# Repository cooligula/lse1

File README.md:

View this project on [CADLAB.io](https://cadlab.io/project/29478). 

# LSE1
> [!CAUTION]
> **NO FABRICAR** 

Aquesta PCB no respecta les regles de disseny de SafePCB donat que es va fer per a ser fabricada amb JLCPCB durant l'estiu.

A més, per tal com estan definits els rangs de preu a JLCPCB, es va prendre la decisió conscient de fer la placa més gran que el que es demana a l'assignatura, ja que no suposava un sobrecost si no superava els 100mm x 100mm.

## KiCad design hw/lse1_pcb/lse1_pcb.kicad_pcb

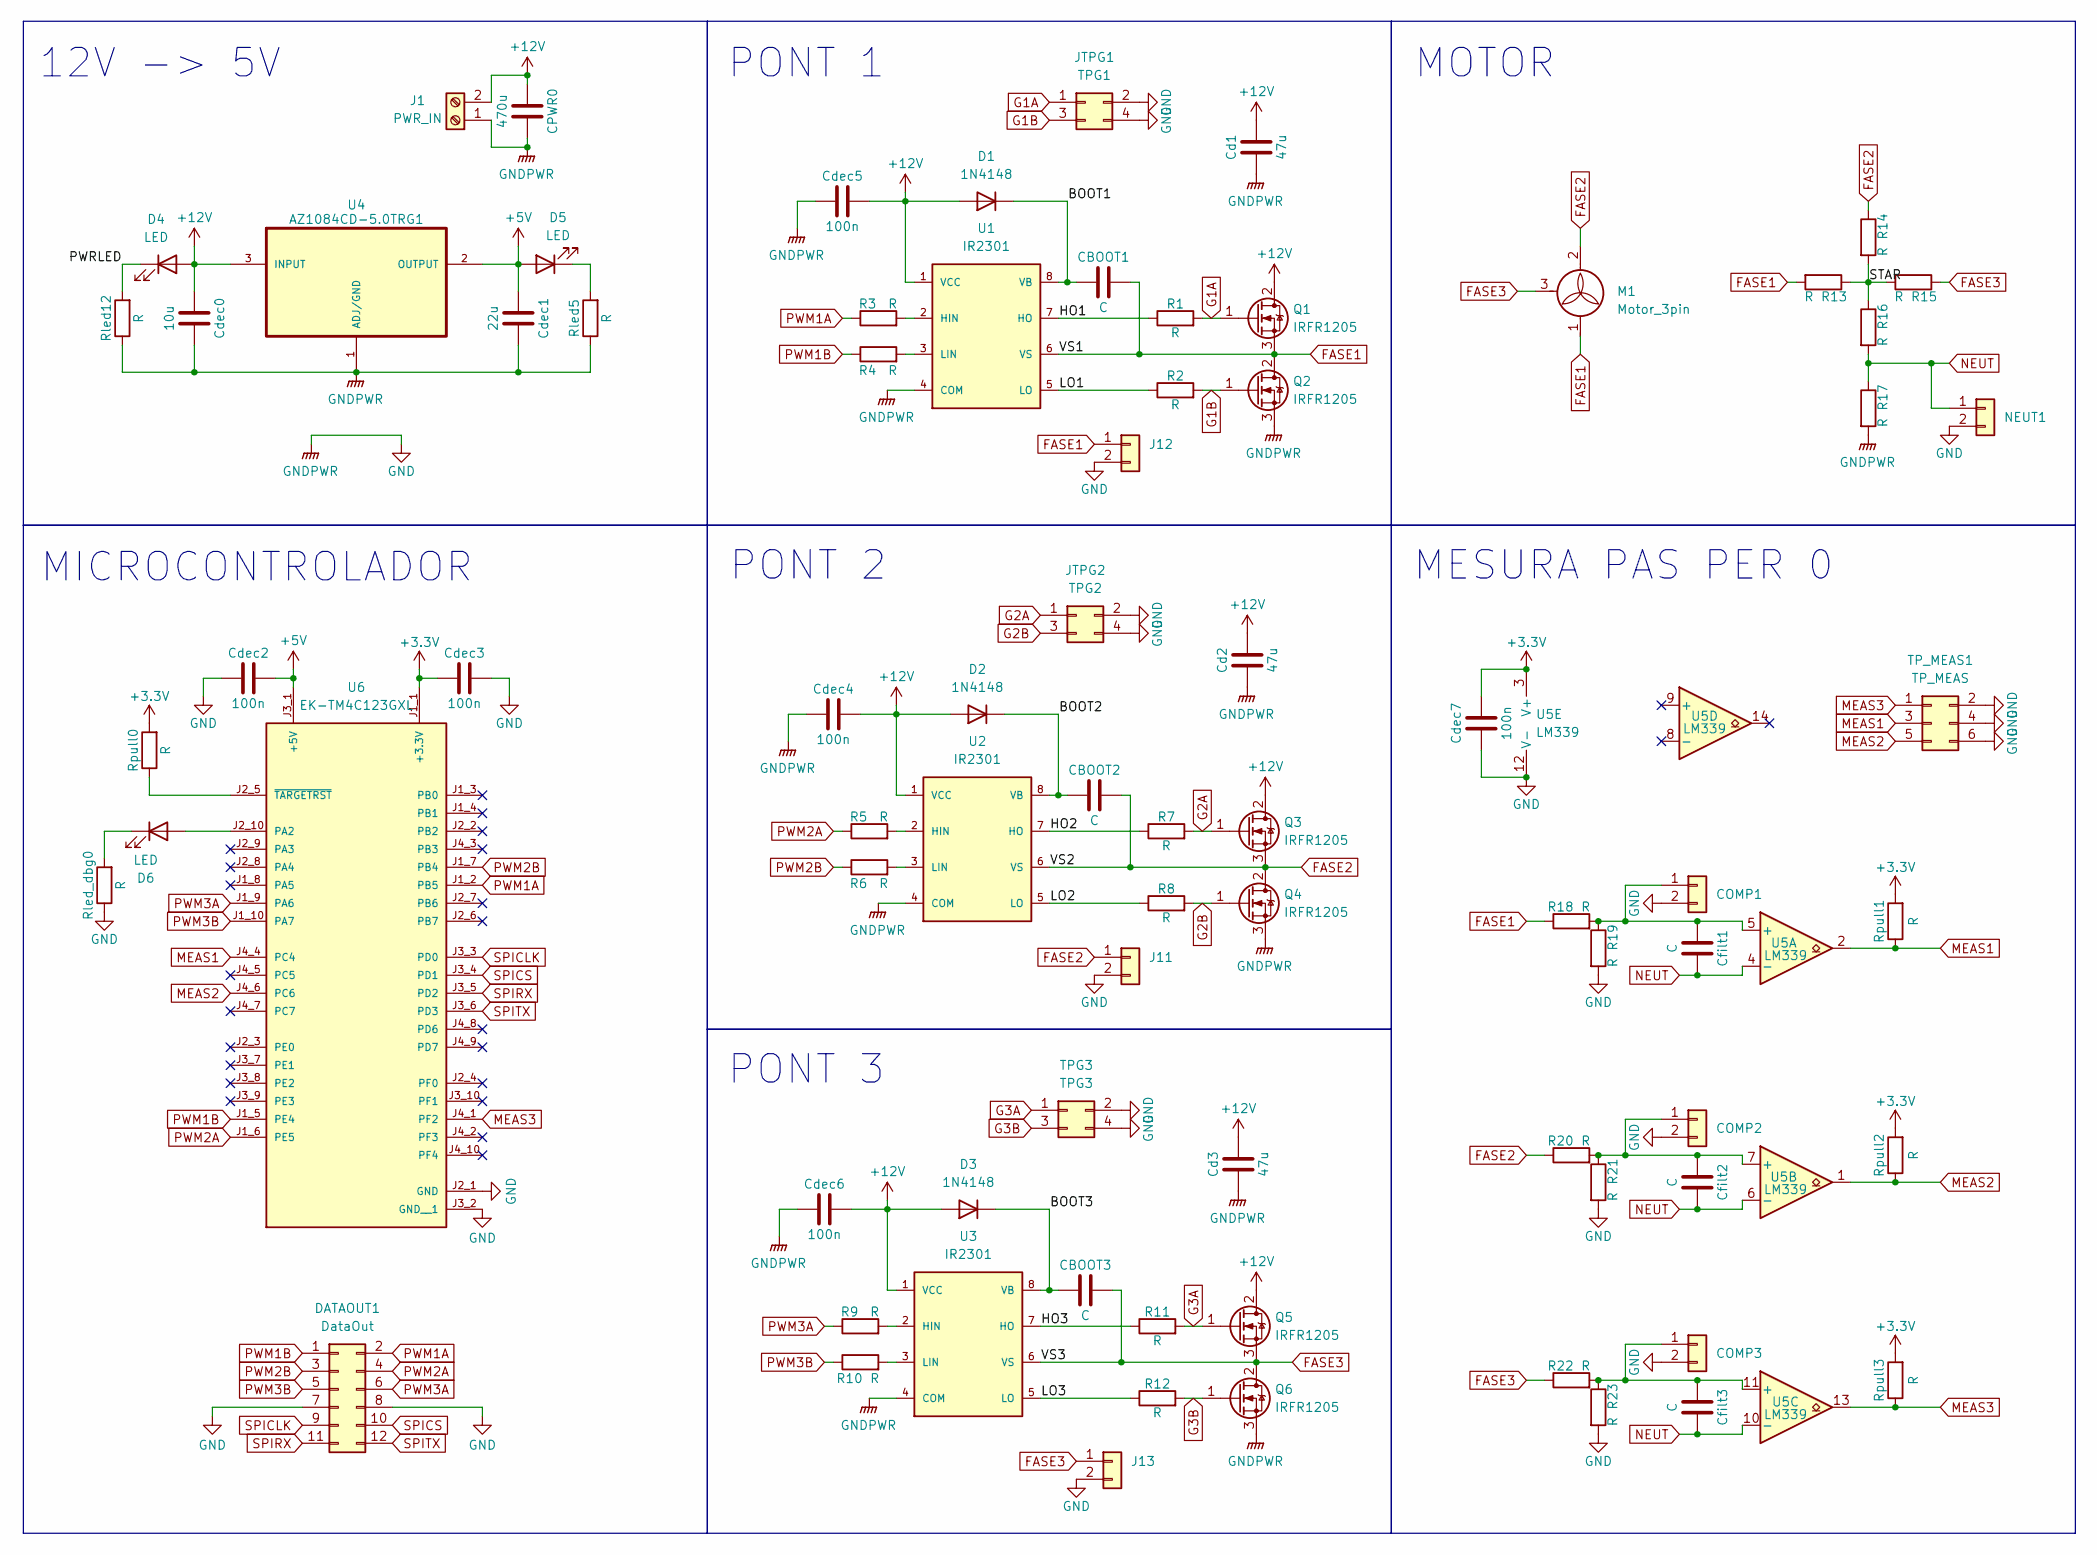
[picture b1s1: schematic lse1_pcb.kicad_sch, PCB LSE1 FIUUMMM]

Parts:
CBOOT1, CBOOT2, CBOOT3: C; C_1206_3216Metric
COMP1: TP_DIV1; PinHeader_1x02_P2.54mm_Vertical
COMP2: TP_DIV2; PinHeader_1x02_P2.54mm_Vertical
COMP3: TP_DIV3; PinHeader_1x02_P2.54mm_Vertical
CPWR0: 470u; C_Elec_10x10.2
Cd1, Cd2, Cd3: 47u; C_1206_3216Metric
Cdec0: 10u; C_1206_3216Metric
Cdec1: 22u; C_1206_3216Metric
Cdec2, Cdec3, Cdec4, Cdec5, Cdec6, Cdec7: 100n; C_1206_3216Metric
Cfilt1, Cfilt2, Cfilt3: C; C_1206_3216Metric
D1, D2, D3: 1N4148; D_DO-35_SOD27_P7.62mm_Horizontal
D4, D5, D6: LED; LED_0805_2012Metric
DATAOUT1: DataOut; PinHeader_2x06_P2.54mm_Vertical
J1: PWR_IN; Samtec_HPM-02-01-x-S_Straight_1x02_Pitch5.08mm
J11: TP_FASE2; PinHeader_1x02_P2.54mm_Vertical
J12: TP_FASE1; PinHeader_1x02_P2.54mm_Vertical
J13: TP_FASE3; PinHeader_1x02_P2.54mm_Vertical
JTPG1: TPG1; PinHeader_1x04_P2.54mm_Vertical
JTPG2: TPG2; PinHeader_1x04_P2.54mm_Vertical
M1: Motor_3pin; Samtec_HPM-03-01-x-S_Straight_1x03_Pitch5.08mm
NEUT1: TP_NEUT; PinHeader_1x02_P2.54mm_Vertical
Q1, Q2, Q3, Q4, Q5, Q6: IRFR1205; TO-252-2
R1, R2, R3, R4, R5, R6, R7, R8, R9, R10, R11, R12, R13, R14, R15, R16, R17, R18, R19, R20, R21, R22, R23: R; R_1206_3216Metric
Rled5, Rled12: R; R_1206_3216Metric
Rled_dbg0: R; R_1206_3216Metric
Rpull0, Rpull1, Rpull2, Rpull3: R; R_1206_3216Metric
TPG3: TPG3; PinHeader_1x04_P2.54mm_Vertical
TP_MEAS1: TP_MEAS; PinHeader_2x03_P2.54mm_Vertical
U1, U2, U3: IR2301; SOIC-8_3.9x4.9mm_P1.27mm
U4: AZ1084CD-5.0TRG1; DPAK457P1010X238-3N
U5: LM339; SOIC-14_3.9x8.7mm_P1.27mm
U6: EK-TM4C123GXL; MODULE_EK-TM4C123GXL; PARTREV April 2013

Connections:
+3.3V: Cdec3.1, Cdec7.2, Rpull0.2, Rpull1.2, Rpull2.2, Rpull3.2, U5.3 (V+), U6.J1_1 (+3.3V)
+5V: Cdec1.1, Cdec2.2, D5.2 (A), U4.2 (OUTPUT), U6.J3_1 (+5V)
+12V: CPWR0.1, Cd1.2, Cd2.2, Cd3.2, Cdec0.1, Cdec4.2, Cdec5.2, Cdec6.2, D1.2 (A), D2.2 (A), D3.2 (A), D4.2 (A), J1.2, Q1.2 (D), Q3.2 (D), Q5.2 (D), U1.1 (VCC), U2.1 (VCC), U3.1 (VCC), U4.3 (INPUT)
/BOOT1: CBOOT1.1, D1.1 (K), U1.8 (VB)
/BOOT2: CBOOT2.1, D2.1 (K), U2.8 (VB)
/BOOT3: CBOOT3.1, D3.1 (K), U3.8 (VB)
/HO1: R1.1, U1.7 (HO)
/HO2: R7.1, U2.7 (HO)
/HO3: R11.1, U3.7 (HO)
/LO1: R2.1, U1.5 (LO)
/LO2: R8.1, U2.5 (LO)
/LO3: R12.1, U3.5 (LO)
/PWRLED: D4.1 (K), Rled12.2
/STAR: R13.1, R14.2, R15.2, R16.1
FASE1: CBOOT1.2, J12.1, M1.1, Q1.3 (S), Q2.2 (D), R13.2, R18.1, U1.6 (VS)
FASE2: CBOOT2.2, J11.1, M1.2, Q3.3 (S), Q4.2 (D), R14.1, R20.1, U2.6 (VS)
FASE3: CBOOT3.2, J13.1, M1.3, Q5.3 (S), Q6.2 (D), R15.1, R22.1, U3.6 (VS)
G1A: JTPG1.1, Q1.1 (G), R1.2
G1B: JTPG1.3, Q2.1 (G), R2.2
G2A: JTPG2.1, Q3.1 (G), R7.2
G2B: JTPG2.3, Q4.1 (G), R8.2
G3A: Q5.1 (G), R11.2, TPG3.1
G3B: Q6.1 (G), R12.2, TPG3.3
GND: COMP1.2, COMP2.2, COMP3.2, CPWR0.2, Cd1.1, Cd2.1, Cd3.1, Cdec0.2, Cdec1.2, Cdec2.1, Cdec3.2, Cdec4.1, Cdec5.1, Cdec6.1, Cdec7.1, DATAOUT1.7, DATAOUT1.8, J1.1, J11.2, J12.2, J13.2, JTPG1.2, JTPG1.4, JTPG2.2, JTPG2.4, NEUT1.2, Q2.3 (S), Q4.3 (S), Q6.3 (S), R17.2, R19.2, R21.2, R23.2, Rled5.1, Rled12.1, Rled_dbg0.1, TPG3.2, TPG3.4, TP_MEAS1.2, TP_MEAS1.4, TP_MEAS1.6, U1.4 (COM), U2.4 (COM), U3.4 (COM), U4.1 (ADJ/GND), U5.12 (V-), U6.J2_1 (GND), U6.J3_2 (GND__1); also elsewhere on the board
MEAS1: Rpull1.1, TP_MEAS1.3, U5.2, U6.J4_4 (PC4); also elsewhere on the board
MEAS2: Rpull2.1, TP_MEAS1.5, U5.1, U6.J4_6 (PC6); also elsewhere on the board
MEAS3: Rpull3.1, TP_MEAS1.1, U5.13, U6.J4_1 (PF2); also elsewhere on the board
NEUT: Cfilt1.2, Cfilt2.2, Cfilt3.2, NEUT1.1, R16.2, R17.1, U5.4 (-), U5.6 (-), U5.10 (-)
unnamed: COMP1.1, Cfilt1.1, R18.2, R19.1, U5.5 (+)
unnamed: COMP2.1, Cfilt2.1, R20.2, R21.1, U5.7 (+)
unnamed: COMP3.1, Cfilt3.1, R22.2, R23.1, U5.11 (+)
unnamed: D5.1 (K), Rled5.2
unnamed: D6.2 (A), U6.J2_10 (PA2)
unnamed: D6.1 (K), Rled_dbg0.2
unnamed: R3.2, U1.2 (HIN)
unnamed: R4.2, U1.3 (LIN)
unnamed: R5.2, U2.2 (HIN)
unnamed: R6.2, U2.3 (LIN)
unnamed: R9.2, U3.2 (HIN)
unnamed: R10.2, U3.3 (LIN)
unnamed: Rpull0.1, U6.J2_5 (~TARGETRST)
PWM1A: DATAOUT1.2, R3.1, U6.J1_2 (PB5)
PWM1B: DATAOUT1.1, R4.1, U6.J1_5 (PE4)
PWM2A: DATAOUT1.4, R5.1, U6.J1_6 (PE5)
PWM2B: DATAOUT1.3, R6.1, U6.J1_7 (PB4)
PWM3A: DATAOUT1.6, R9.1, U6.J1_9 (PA6)
PWM3B: DATAOUT1.5, R10.1, U6.J1_10 (PA7)
SPICLK: DATAOUT1.9, U6.J3_3 (PD0)
SPICS: DATAOUT1.10, U6.J3_4 (PD1)
SPIRX: DATAOUT1.11, U6.J3_5 (PD2)
SPITX: DATAOUT1.12, U6.J3_6 (PD3)

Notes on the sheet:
PONT 1
12V -> 5V
MOTOR
PONT 3
MESURA PAS PER 0
PONT 2
MICROCONTROLADOR

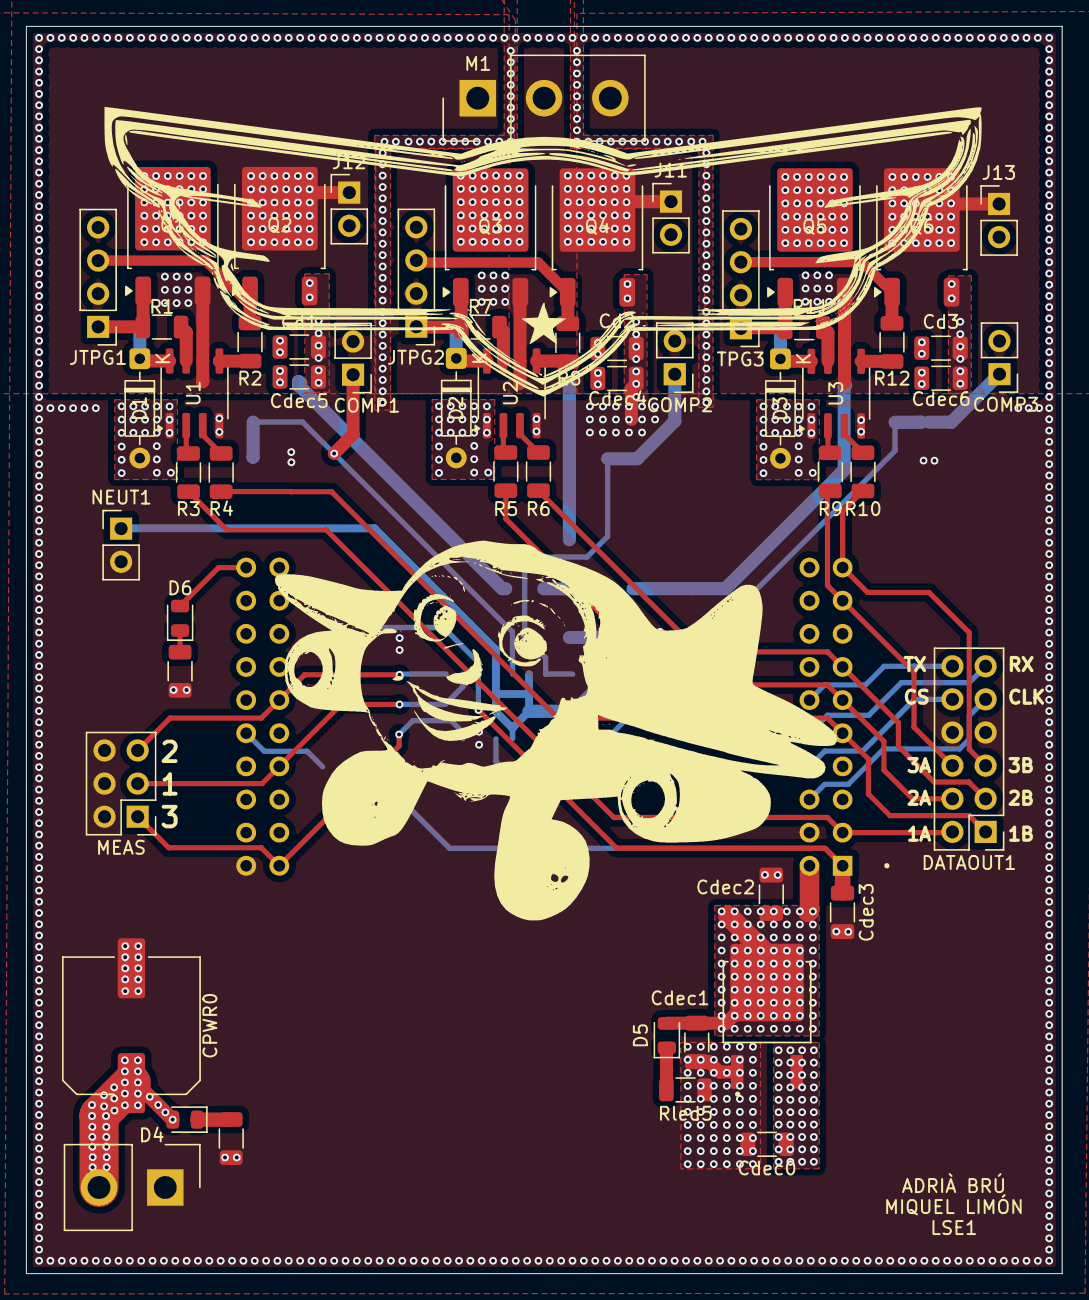
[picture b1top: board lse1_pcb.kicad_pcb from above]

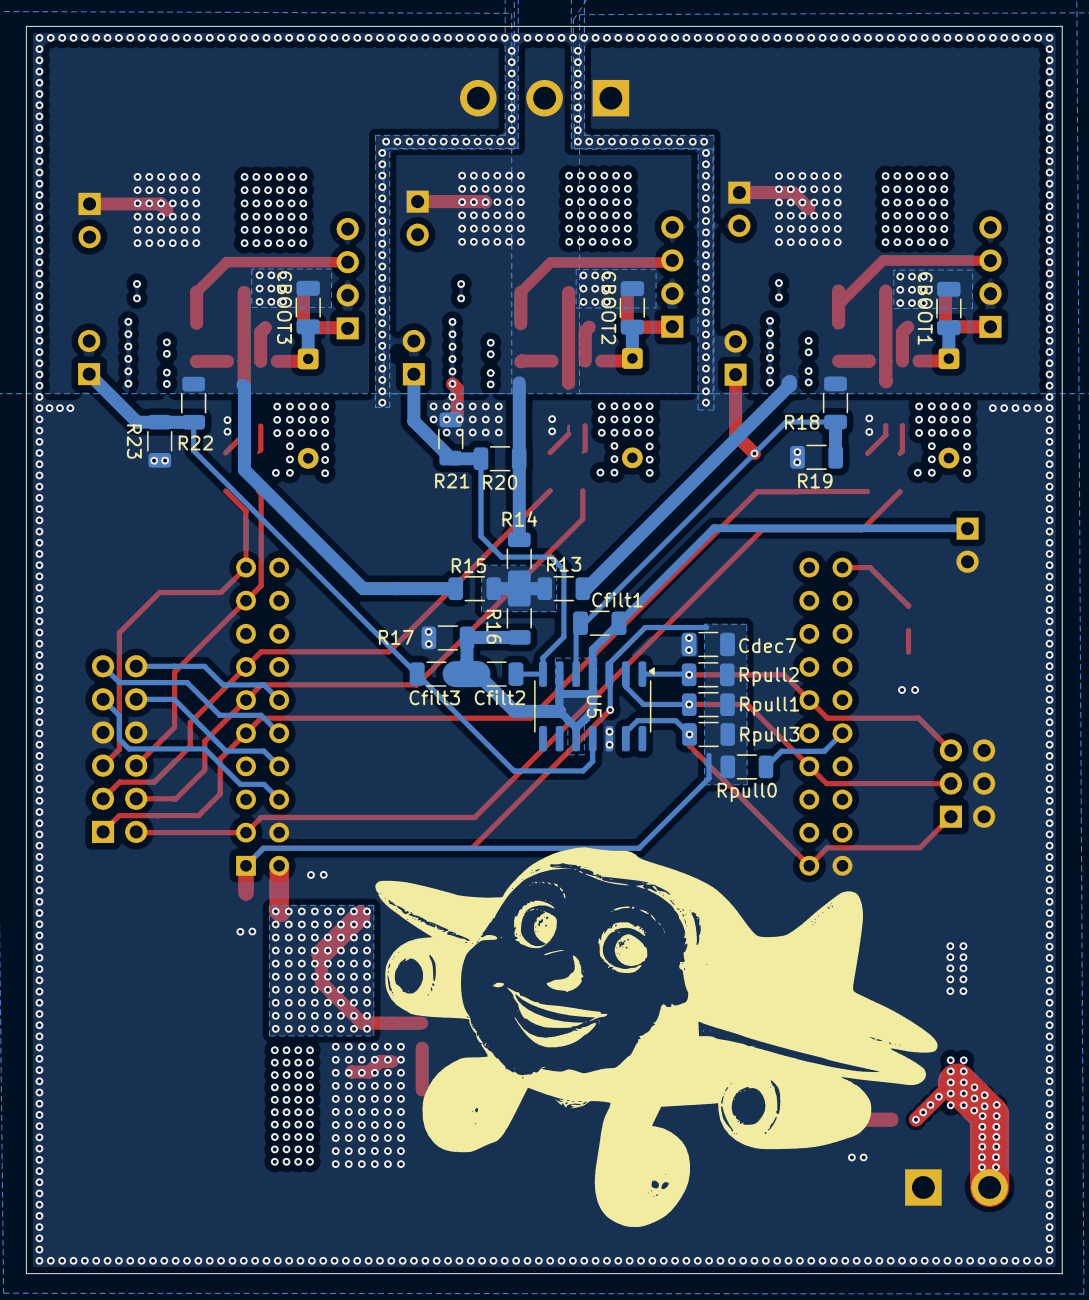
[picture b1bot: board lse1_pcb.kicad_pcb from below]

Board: 4 copper layers, 79.4 x 95.6 mm, 80 parts (23 on the bottom side), 51 nets.

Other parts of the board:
MEAS: TP_MEAS; PinHeader_2x03_P2.54mm_Vertical

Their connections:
GND: MEAS.2, MEAS.4, MEAS.6; also elsewhere on the board
MEAS1: MEAS.3; also elsewhere on the board
MEAS2: MEAS.5; also elsewhere on the board
MEAS3: MEAS.1; also elsewhere on the board

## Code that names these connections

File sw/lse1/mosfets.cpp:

#include "mosfets.h"
#include "driverlib/pin_map.h"

void MosfetController::setup(uint32_t pwm_freq, float duty_cycle)
{
    // The PWM peripheral must be enabled for use.
    // Habilitem els moduls 0 i 1 pq els necessitem els dos
    MAP_SysCtlPeripheralEnable(SYSCTL_PERIPH_PWM0);
    MAP_SysCtlPeripheralEnable(SYSCTL_PERIPH_PWM1);

    // Enable the GPIO port that is used for the PWM output.
    MAP_SysCtlPeripheralEnable(SYSCTL_PERIPH_GPIOA);
    MAP_SysCtlPeripheralEnable(SYSCTL_PERIPH_GPIOB);
    MAP_SysCtlPeripheralEnable(SYSCTL_PERIPH_GPIOE);

    // Wait for peripherals to be ready
    while(!MAP_SysCtlPeripheralReady(SYSCTL_PERIPH_GPIOA) ||
          !MAP_SysCtlPeripheralReady(SYSCTL_PERIPH_GPIOB) ||
          !MAP_SysCtlPeripheralReady(SYSCTL_PERIPH_GPIOE) ||
          !MAP_SysCtlPeripheralReady(SYSCTL_PERIPH_PWM0)  ||
          !MAP_SysCtlPeripheralReady(SYSCTL_PERIPH_PWM1));

    // Configure the PWM function for this pin
    // 1A (High-side)
    MAP_GPIOPinConfigure(GPIO_PB5_M0PWM3);
    MAP_GPIOPinTypePWM(GPIO_PORTB_BASE, GPIO_PIN_5);
    // 2A (High-side)
    MAP_GPIOPinConfigure(GPIO_PE5_M0PWM5);
    MAP_GPIOPinTypePWM(GPIO_PORTE_BASE, GPIO_PIN_5);
    // 3A (High-side)
    MAP_GPIOPinConfigure(GPIO_PA6_M1PWM2);
    MAP_GPIOPinTypePWM(GPIO_PORTA_BASE, GPIO_PIN_6);

    // Enable Low GPIOs
    #ifndef USE_PWM_LOW_SIDE
    MAP_GPIOPinTypeGPIOOutput(LOW_Ph1B_GPIO_BASE, LOW_Ph1B_GPIO_PIN); // 1B (Low-side)
    MAP_GPIOPinTypeGPIOOutput(LOW_Ph2B_GPIO_BASE, LOW_Ph2B_GPIO_PIN); // 2B (Low-side)
    MAP_GPIOPinTypeGPIOOutput(LOW_Ph3B_GPIO_BASE, LOW_Ph3B_GPIO_PIN); // 3B (Low-side)
    #else
    // 1B (Low-side) - PE4 (M0PWM4)
    MAP_GPIOPinConfigure(GPIO_PE4_M0PWM4);
    MAP_GPIOPinTypePWM(GPIO_PORTE_BASE, GPIO_PIN_4);
    // 2B (Low-side) - PB4 (M0PWM2)
    MAP_GPIOPinConfigure(GPIO_PB4_M0PWM2);
    MAP_GPIOPinTypePWM(GPIO_PORTB_BASE, GPIO_PIN_4);
    // 3B (Low-side) - PA7 (M1PWM3)
    MAP_GPIOPinConfigure(GPIO_PA7_M1PWM3);
    MAP_GPIOPinTypePWM(GPIO_PORTA_BASE, GPIO_PIN_7);
    #endif


    // Configure PWM0 to count up/down without synchronization.
    MAP_PWMGenConfigure(PWM0_BASE, PWM_GEN_1, PWM_GEN_MODE_UP_DOWN |
                        PWM_GEN_MODE_NO_SYNC); // 1A (M0PWM3), 2B (M0PWM2)
    MAP_PWMGenConfigure(PWM0_BASE, PWM_GEN_2, PWM_GEN_MODE_UP_DOWN |
                        PWM_GEN_MODE_NO_SYNC); // 1B (M0PWM4), 2A (M0PWM5)
    MAP_PWMGenConfigure(PWM1_BASE, PWM_GEN_1, PWM_GEN_MODE_UP_DOWN |
                        PWM_GEN_MODE_NO_SYNC); // 3A (M1PWM2), 3B (M1PWM3)

    // Period in clock ticks
    uint32_t ui32Period = (MAP_SysCtlClockGet() / pwm_freq);
    
    // Period for all three generators
    MAP_PWMGenPeriodSet(PWM0_BASE, PWM_GEN_1, ui32Period); // Gen 1 (1A, 2B)
    MAP_PWMGenPeriodSet(PWM0_BASE, PWM_GEN_2, ui32Period); // Gen 2 (1B, 2A)
    MAP_PWMGenPeriodSet(PWM1_BASE, PWM_GEN_1, ui32Period); // Gen 1 (3A, 3B)
    
    // Pulse width in clock ticks
    uint32_t ui32Width = (uint32_t)(ui32Period * duty_cycle);

    // Pulse Width for all three outputs
    MAP_PWMPulseWidthSet(PWM0_BASE, PWM_OUT_3, ui32Width); // 1A (PB5)
    MAP_PWMPulseWidthSet(PWM0_BASE, PWM_OUT_5, ui32Width); // 2A (PE5)
    MAP_PWMPulseWidthSet(PWM1_BASE, PWM_OUT_2, ui32Width); // 3A (PA6)

    // Set pulse widths for low-side if they are PWMs
    #ifdef USE_PWM_LOW_SIDE
    MAP_PWMPulseWidthSet(LOW_Ph1B_PWM_BASE, LOW_Ph1B_PWM_OUT_BIT, ui32Width); // 1B (PE4)
    MAP_PWMPulseWidthSet(LOW_Ph2B_PWM_BASE, LOW_Ph2B_PWM_OUT_BIT, ui32Width); // 2B (PB4)
    MAP_PWMPulseWidthSet(LOW_Ph3B_PWM_BASE, LOW_Ph3B_PWM_OUT_BIT, ui32Width); // 3B (PA7)
    #endif

    // Enable PWM generators
    MAP_PWMGenEnable(PWM0_BASE, PWM_GEN_1);
    MAP_PWMGenEnable(PWM0_BASE, PWM_GEN_2);
    MAP_PWMGenEnable(PWM1_BASE, PWM_GEN_1);
}

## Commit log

2025-07-15 Backlink to CADLAB.io has been added.
2025-07-15 schem done
2025-07-16 difference describe/commit?
2025-07-16 added launchpad footprint
2025-07-16 ponts fets
2025-07-16 pcb done
2025-07-16 done?
2025-07-16 copper pours i algunes modificacions
2025-07-16 measures
2025-07-17 restore backup, design up-to-date
2025-07-17 close to finish
2025-07-17 drc passed, only pwr in missing
2025-07-17 vias
2025-07-17 should be done?
2025-07-17 names x)
2025-08-05 start code project + correct pcb
2025-08-15 update silkscreen
2025-08-15 push
2025-08-15 finish silkscreen
2025-08-15 backups
2025-10-08 update readme CAUTION
2025-10-08 pcb name
2025-10-08 last min
2025-11-19 closed loop done
2025-11-25 OL + CL v1
2025-11-26 added phase test file and changed phase names (Ph1A -> 1A)
2025-12-09 coses
2025-12-17 sortida lse1
2026-01-19 posant coses al dia
2026-01-26 CL acabat, cal canviar C de placa i revisar stall
2026-01-27 dimarts
2026-01-27 poor man's PID
2026-01-28 dynamic blanking
2026-02-08 PID v1, falla potenciometre
2026-02-09 PID seems okayish
2026-02-09 advance, doesn't seem to heat up as much
2026-02-11 FUNCIONA
2026-02-11 per si acas
2026-04-21 primer esbos SPI
2026-05-30 codi LSE1 retocat + motors calibrats
